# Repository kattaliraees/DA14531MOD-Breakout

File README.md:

# DA14531MOD-Breakout
DA14531MOD-Breakout board

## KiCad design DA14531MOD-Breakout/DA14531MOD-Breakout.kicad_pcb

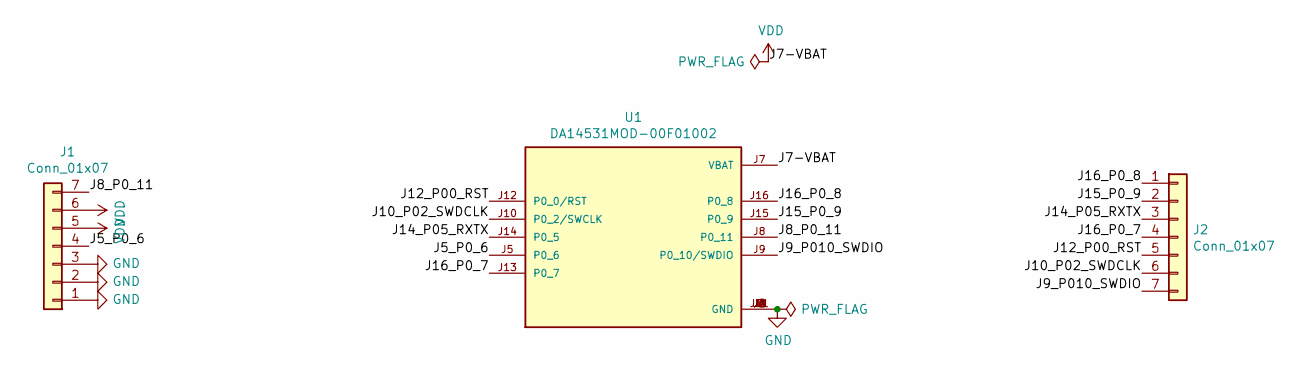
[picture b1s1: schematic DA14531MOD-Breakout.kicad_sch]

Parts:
J1, J2: Conn_01x07; PinHeader_1x07_P2.54mm_Vertical
U1: DA14531MOD-00F01002; XCVR_DA14531MOD-00F01002; PARTREV 1.0

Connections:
/J5_P0_6: J1.4, U1.J5 (P0_6)
/J8_P0_11: J1.7, U1.J8 (P0_11)
/J9_P010_SWDIO: J2.7, U1.J9 (P0_10/SWDIO)
/J10_P02_SWDCLK: J2.6, U1.J10 (P0_2/SWCLK)
/J12_P00_RST: J2.5, U1.J12 (P0_0/RST)
/J14_P05_RXTX: J2.3, U1.J14 (P0_5)
/J15_P0_9: J2.2, U1.J15 (P0_9)
/J16_P0_7: J2.4, U1.J13 (P0_7)
/J16_P0_8: J2.1, U1.J16 (P0_8)
GND: J1.1, J1.2, J1.3, U1.J1 (GND), U1.J2 (GND), U1.J3 (GND), U1.J4 (GND), U1.J6 (GND), U1.J11 (GND)
VDD: J1.5, J1.6, U1.J7 (VBAT)

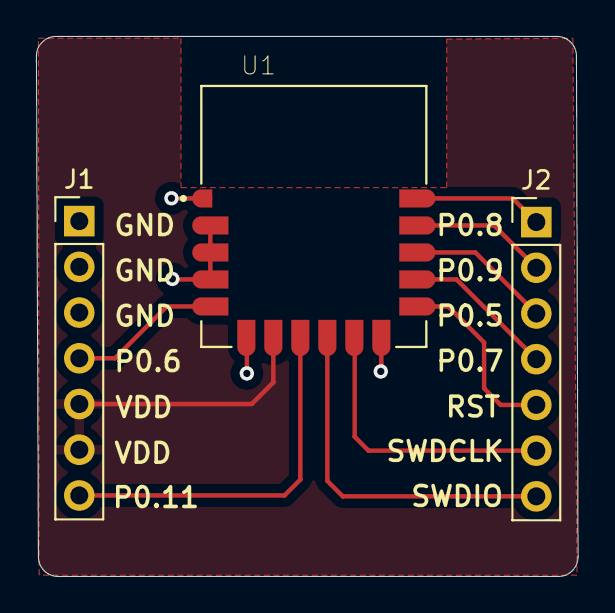
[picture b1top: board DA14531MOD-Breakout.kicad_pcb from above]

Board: 2 copper layers, 30.1 x 30.0 mm, 3 parts (0 on the bottom side), 11 nets.

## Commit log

2021-02-18 initial
2021-02-18 dekl
2021-02-18 finetuning
2021-02-18 gerber
2021-02-24 updated 3d model
2023-04-04 kicad v7
